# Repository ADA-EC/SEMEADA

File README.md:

# 🤖 SEMEADA

## O que é o projeto?
O projeto, desenvolvido pela [ADA](http://adaec.icmc.usp.br/sobre-nos/) em parceria com o [SEMEAR](https://semear.eesc.usp.br/), se trata de um robô de mesa capaz de captar comandos de fala e interpretá-los, por meio de **processamento de linguagem natural**, para realizar ações. Até o momento, o robô é capaz de obedecer aos seguintes comandos:
* Dançar
* Acordar
* Dormir
* Girar
* Levantar os braços
* Contar uma piada
* Falar sobre seu atual estado emocional
* Se apresentar
* Falar sobre a ADA
* Falar sobre o SEMEAR
* Tocar uma música
* Soletrar uma palavra
* Falar sobre o projeto

Além disso, o robô, através de máquinas de estado, possui a habilida de **simular sentimentos**, tendo assim um **"estado de espírito"**.

A seguir descrevemos mais detalhadamente o funcionamento do projeto.

## Funcionamento
Quando o robô é inicializado, o mesmo fica em estado de espera, aguardando o acionamento. Quando recebe a mensagem "Ouvir", inicia a captação de áudio (posteriormente será utilizado um botão para iniciar a captação). O áudio é armazenado em uma faixa de som (audio.wav) posteriormente enviada para `processamento_voz.py`, que utiliza a biblioteca `speech_recognition` para transformar o áudio captado em texto. O texto então é submetido 

## Executando o projeto
### Treinando o modelo
Para treinar o modelo utilizar as instruções contidas [nesse guia](https://github.com/ADA-EC/SEMEADA/tree/main/Treinamento_PLN)

### Rodando o código
Para rodar o projeto, executar o comando: <br>
`python Esqueleto/main.py`

## Estrutura de pastas do projeto
- 📁 Codigo ➡️ contém arquivos de estudo do início do projeto
- 📁 Esqueleto ➡️ contém todo o código do robô
  - 🐍`comandos.py` ➡️ mapemaneto dos comandos em números, chamado pelo PLN
  - 🐍`commSerial.py` ➡️ faz a comunicação do código python com o Arduino, chamada pela máquina de estados
  - 🐍`main.py` ➡️ coordena todas as funções do robô
    - inicializa o robô
    - chama o processamento de áudio
    - recebe o texto de volta
    - envia o texto para o processamento
    - recebe o número do comando
    - envia para a máquina de estados   
  - 🐍`olhos.py` ➡️ mapeamento dos olhos para cada estado de humor
  - 🐍`PLN.py` ➡️ recebe o texto da *main*, faz o pré processamento do texto, submete ao modelo, retorna o valor do comando para a *main*
  - 🐍`processamento_voz.py` ➡️ chamada pela *main*, capta o áudio, transforma em texto e retorna para a *main*
  - 🐍`rostos.py` ➡️ faz a conexão com o arduino (não sei se está sendo utilizada, verificar remoção)
  - 🐍`sintese_voz.py` ➡️ usado para repetir o comando de voz de volta (verificar remoção)
  - 🐍`state_machine.py` ➡️ controla o estado de humor do robô, gerencia execução dos comandos (recebe da *main* o comando e envia para *commSerial*)
- 📁 Falhas_treinamento_PLN ➡️ contém o histórico de tentativas de treinamento do modelo
- 📁 Gravar ➡️ armazena o arquivo de áudio captado
- 📁 Maquina_Estados ➡️ contém as imagens das máquinas de estados desenvolvidas no JFLAP
- 📁 Olhos ➡️ contém os arquivos com as imagens usada para teste das telas LCD
- 📁 PCB ➡️ contém o projeto das placas do robô
- 📁 Testes Arduino ➡️ contém os arquivos comunicação com os componentes físicos do robô
- 📁 Treinamento_PLN ➡️ contém os arquivos de treinamento do modelo de processamento de linguagem natural

## O hardware

## Tecnologias Usadas

### Bibliotecas utilizadas
A seguir uma lista das bibliotecas utilizadas e como fazer sua instalação, além de dicas para contornar possíveis erros durante a instalação. (Todas as instalações foram feitas utilizando o pip, não usar o WSL)
- Pandas <br>
  `pip install pandas`
- SpaCy <br>
  `pip install spacy`
- Seaborn <br>
  `pip install seaborn`
- SpaCy Language Detector <br>
  `pip install spacy-langdetect`
- SpaCy pt_core_news_sm <br>
  `python -m spacy download pt_core_news_sm`
- gTTS <br>
  `pip install gTTS`
- SpeechRecognition [Caso não dê certo, tente rodar “pip3 install SpeechRecognition”] <br>
  `pip install SpeechRecognition`
- PlaySound [Caso não dê certo, tente dar um downgrade para a versão 1.2.2 (pip install playsound==1.2.2)] <br>
  `pip install playsound==1.2.2`
- PyDub <br>
  `pip install pydub`
- SoundDevice <br>
  `pip install sounddevice`
- SoundFile <br>
  `pip install SoundFile`
- Pyserial <br>
  `pip install pyserial`
- PyAudio <br>
  `pip install pyaudio`

### Máquina de Estados
Para realizar o projeto, fizemos algumas máquinas de estados modificadas que indicam o estado do robô após realizar os comandos.
Um exemplo disso é a maquina de estado desenvolvida para vários comandos diversos, mostrada abaixo. Nela, após realizar um comando como dançar, ele fica automaticamente no estado de "feliz".

Além disso, nota-se na imagem que alguns comandos não serão obedecidos se o robô estiver em determinado estado emocional, como o comando "dançar" também, que só pode ser realizado quando este está "feliz", "neutro" ou "triste".

Alguns comentários foram adicionados aos desenhos, para facilitar compreensão e auxiliar no entendimento na hora de construir o código em Python. Um exemplo de comentário pode ser visto na imagem abaixo, referente à máquina de estados "Tocar música".

## Membros
- [Érika Hortência](https://github.com/erika-hortencia)
- [Gabriela Barion Vidal](https://github.com/GabrielaVidal7)
- [Rodrigo Bragato Piva](https://github.com/Rodrigo-P)
- Marcos Almeida

## Agradecimentos
- [Victor Amaral](https://github.com/felfipe)
- [Breno Seixas]([https://github.com/TsuyoshiSonobe](https://github.com/TheGuardianB))
- [Tsuyoshi Sonobe](https://github.com/TsuyoshiSonobe)
- [Pedro Torrente](https://github.com/pdrtorrente)
- Manuella Porto

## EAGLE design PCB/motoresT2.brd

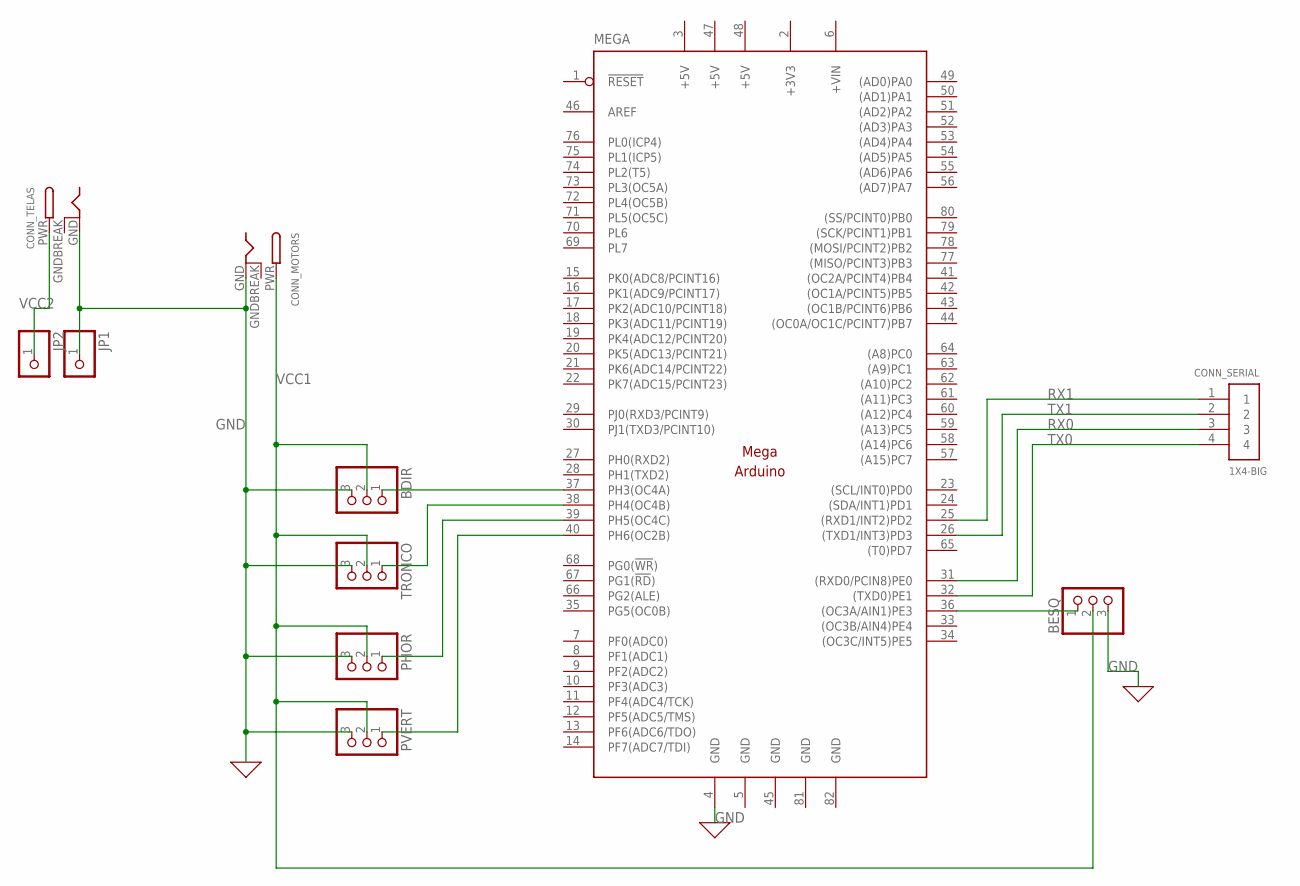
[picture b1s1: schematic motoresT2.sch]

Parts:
BDIR: PINHD-1X3; 1X03
BESQ: PINHD-1X3; 1X03
CONN_MOTORS: DCBARRELPTH; DCJACK_2MM_PTH
CONN_SERIAL: 1X4-BIG; 1X04-BIG
CONN_TELAS: DCBARRELPTH; DCJACK_2MM_PTH
JP1, JP2: PINHD-1X1; 1X01
MEGA: MEGAARDUINO_11; MEGA_ARDUINO_1
PHOR: PINHD-1X3; 1X03
PVERT: PINHD-1X3; 1X03
TRONCO: PINHD-1X3; 1X03

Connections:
+3V3: MEGA.2 (+3V3)
+5V: MEGA.3 (+5V), MEGA.47 (+5V), MEGA.48 (+5V)
+VIN: MEGA.6 (+VIN)
GND: BDIR.3, BESQ.3, CONN_MOTORS.GND, CONN_TELAS.GND, JP1.1, MEGA.4 (GND), MEGA.5 (GND), MEGA.45 (GND), MEGA.81 (GND), MEGA.82 (GND), PHOR.3, PVERT.3, TRONCO.3
GNDBREAK: CONN_MOTORS.GNDBREAK, CONN_TELAS.GNDBREAK
unnamed: BDIR.1, MEGA.37 (PH3(OC4A))
unnamed: MEGA.38 (PH4(OC4B)), TRONCO.1
unnamed: MEGA.39 (PH5(OC4C)), PHOR.1
unnamed: MEGA.40 (PH6(OC2B)), PVERT.1
unnamed: BESQ.1, MEGA.36 ((OC3A/AIN1)PE3)
RX0: CONN_SERIAL.3, MEGA.31 ((RXD0/PCIN8)PE0)
RX1: CONN_SERIAL.1, MEGA.25 ((RXD1/INT2)PD2)
TX0: CONN_SERIAL.4, MEGA.32 ((TXD0)PE1)
TX1: CONN_SERIAL.2, MEGA.26 ((TXD1/INT3)PD3)
VCC1: BDIR.2, BESQ.2, CONN_MOTORS.PWR, PHOR.2, PVERT.2, TRONCO.2
VCC2: CONN_TELAS.PWR, JP2.1

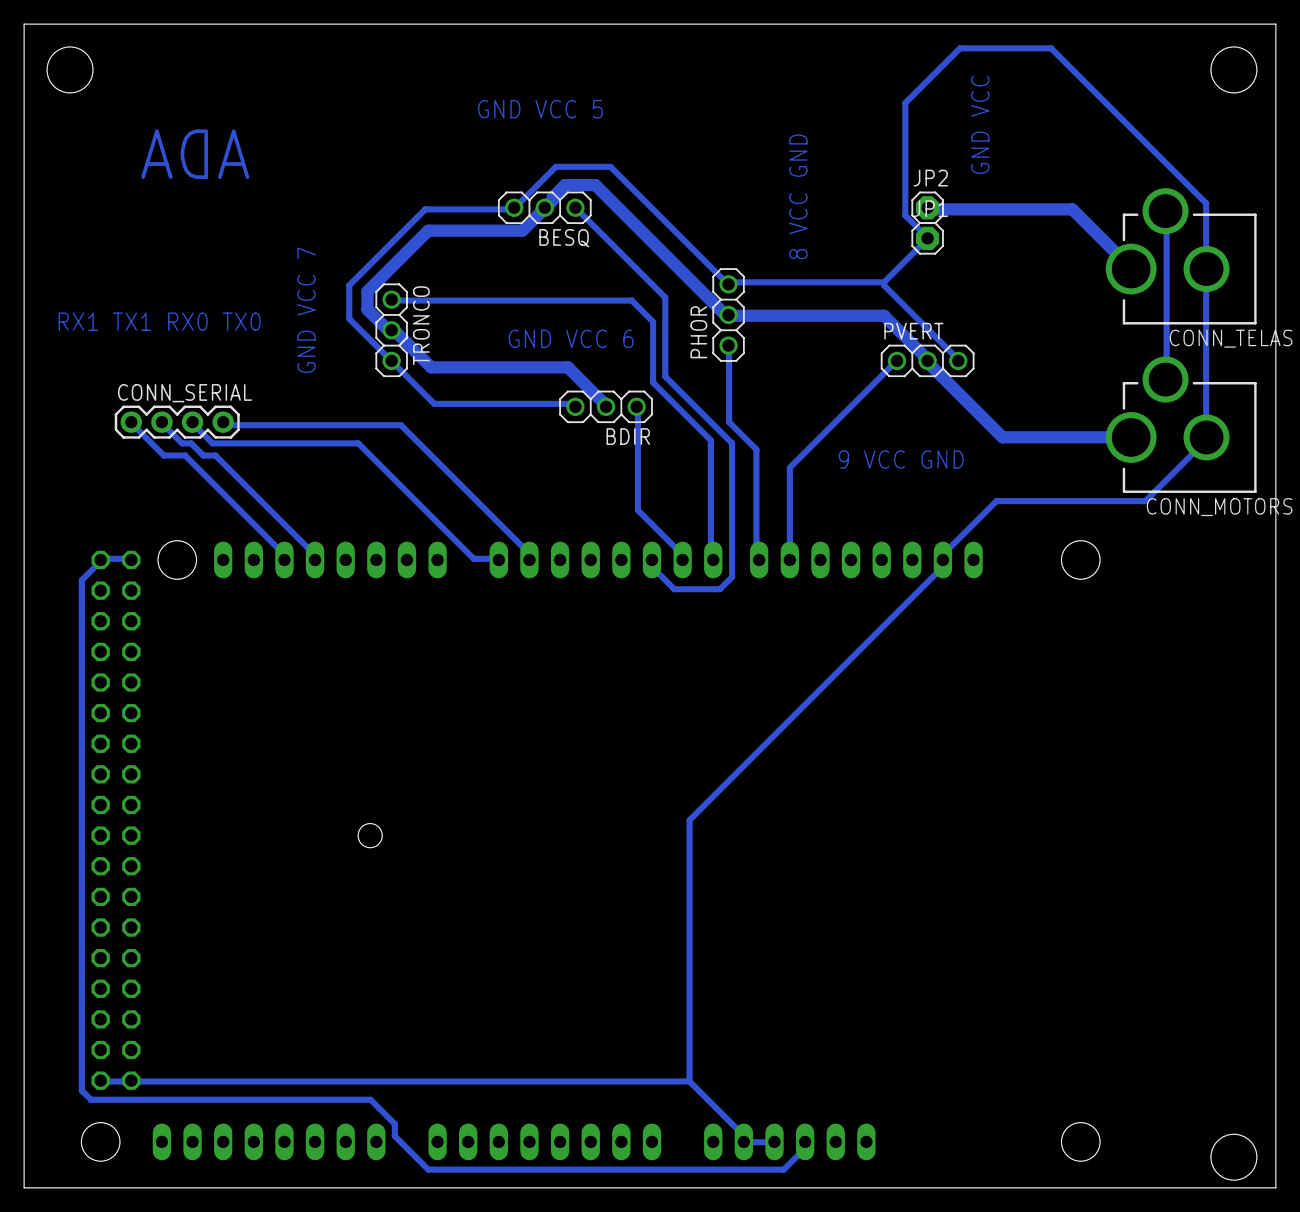
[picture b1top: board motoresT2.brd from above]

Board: 2 copper layers, 103.8 x 96.5 mm, 11 parts (1 on the bottom side), 14 nets.

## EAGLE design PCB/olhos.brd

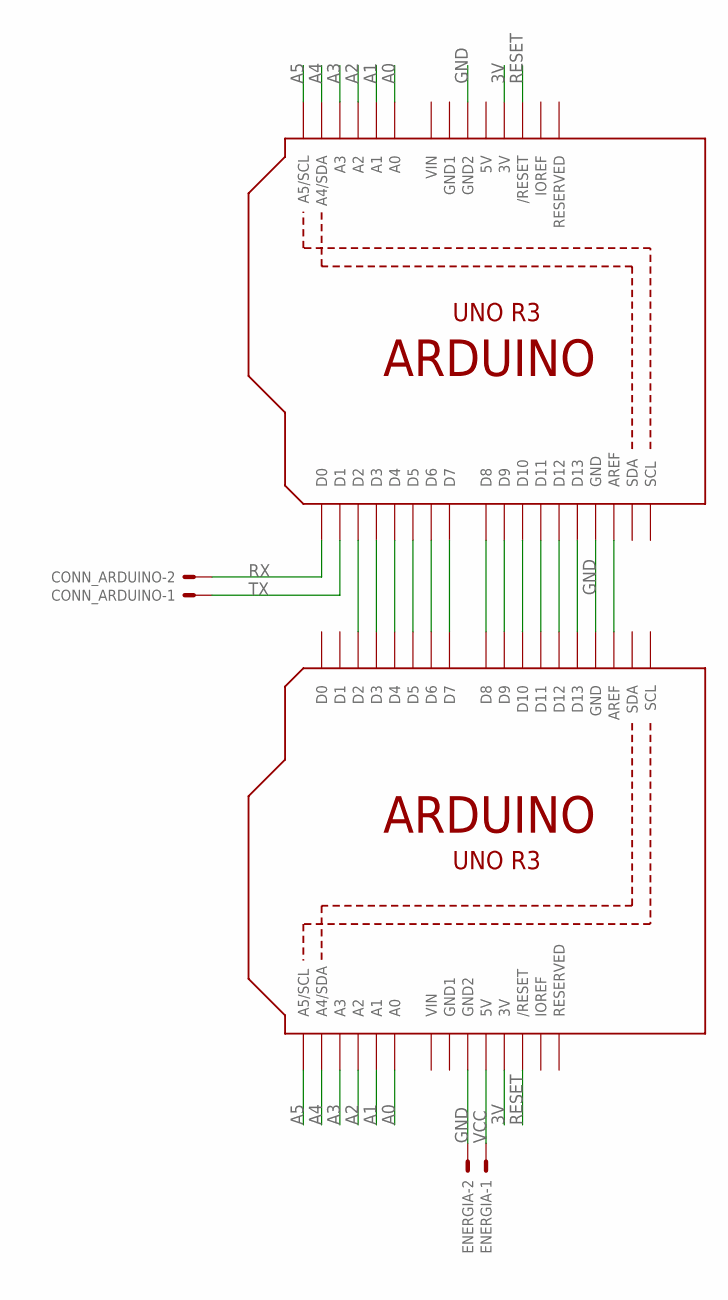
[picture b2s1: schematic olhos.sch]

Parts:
CONN_ARDUINO: 22-23-2021
ENERGIA: 22-23-2021
TELA_LCD: ARDUINOR3-BPLACE
U2: ARDUINOR3-BPLACE

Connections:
3V: TELA_LCD.3V, U2.3V
5V: U2.5V
A0: TELA_LCD.A0, U2.A0
A1: TELA_LCD.A1, U2.A1
A2: TELA_LCD.A2, U2.A2
A3: TELA_LCD.A3, U2.A3
A4: TELA_LCD.A4 (A4/SDA), U2.A4 (A4/SDA)
A5: TELA_LCD.A5 (A5/SCL), U2.A5 (A5/SCL)
GND: ENERGIA.2, TELA_LCD.GND, TELA_LCD.GND2, U2.GND, U2.GND2
GND1: TELA_LCD.GND1, U2.GND1
unnamed: TELA_LCD.D2, U2.D2
unnamed: TELA_LCD.D3, U2.D3
unnamed: TELA_LCD.D4, U2.D4
unnamed: TELA_LCD.D5, U2.D5
unnamed: TELA_LCD.D6, U2.D6
unnamed: TELA_LCD.D7, U2.D7
unnamed: TELA_LCD.D8, U2.D8
unnamed: TELA_LCD.D9, U2.D9
unnamed: TELA_LCD.D10, U2.D10
unnamed: TELA_LCD.D11, U2.D11
unnamed: TELA_LCD.D12, U2.D12
unnamed: TELA_LCD.D13, U2.D13
unnamed: TELA_LCD.AREF, U2.AREF
RESET: TELA_LCD.RESET (/RESET), U2.RESET (/RESET)
RX: CONN_ARDUINO.2, U2.D0
TX: CONN_ARDUINO.1, U2.D1
VCC: ENERGIA.1, TELA_LCD.5V
VIN: TELA_LCD.VIN, U2.VIN

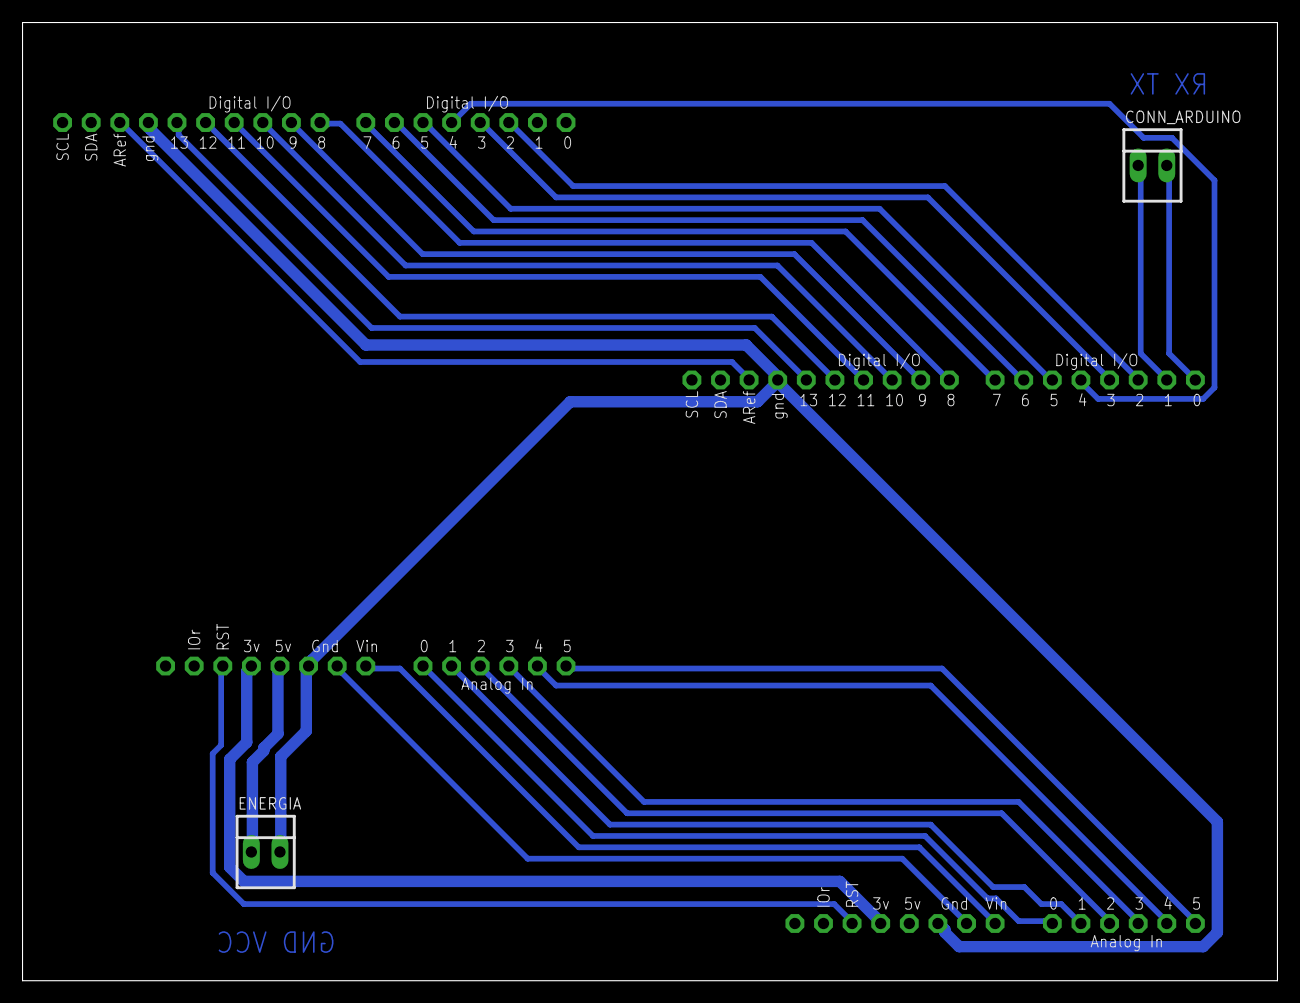
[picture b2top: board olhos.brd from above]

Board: 2 copper layers, 111.4 x 85.1 mm, 4 parts (0 on the bottom side), 27 nets.

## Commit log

2022-05-19 Implementação dos códigos e uso das bibliotecas para comunicação com tela touch
2022-05-20 Código teste para comunicação com o arduino
2022-05-26 arrumando conexão como arduino
2022-06-10 Adicionando commSerial
2022-06-23 arrumando interface face
2022-06-28 Função de enviar mensagem para Arduino criada em Python
2022-07-18 Continuando teste do servo motor
2022-08-17 Arrumando comunicação arduino-Python
2022-08-17 Gitignore
2022-09-02 Controle do Servo
2023-03-21 ultimas atualizacoes
2023-03-21 alterações
2023-03-21 Código descomentado
2023-05-20 Melhoras na conexão com o Arduino
2023-05-28 primeiro intensivão
2023-06-07 PCB dos motores em andamento
2023-06-18 1o prototipo da PCB dos motores finalizado
2023-09-13 PCB olhos pronta
2023-09-16 mudanças
2023-09-16 olho nao usado
2023-09-25 PCB dos olhos reduzida
2023-10-03 Arquivos de impressão da PCB arrumados
2023-10-03 Mais formatos de impressão das PCBs
2023-10-19 State loop fixed
2023-10-19 Added catch and warning in case there's no command for the arduino
2023-10-19 Adicionando imagem para readme
2023-10-19 Redimensionando imagem para readme
2023-10-20 Update README.md
    Adicionando:
    Descrição do projeto
    Funcionamento
    Como rodar o projeto
    Bibliotecas utilizadas
    Estrutura de pastas
2023-10-20 Update README.md
    Adicionando link para instruções de treinamento do modelo
2023-11-16 Simplificando configuração de motores e olhos
2023-11-16 Melhorando funcionamento de piadas e soletrar
2023-11-16 Unificação de Enums e dicionários em arquivo único
2023-12-08 PCD motores arrumada
2023-12-12 PCBs atualizadas
